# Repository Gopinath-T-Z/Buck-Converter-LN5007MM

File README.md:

# DC Buck-Converter (12V–75V → 10V, 400mA)

A KiCad-designed DC buck-boost converter using the LN5007MM PWM 
controller IC.

## Specifications
- Input Voltage  : 12V to 75V
- Output Voltage : 10V (regulated)
- Output Current : 400mA
- Controller IC  : LN5007MM
- Schottky Diode : SS110 (1A / 100V)
- Inductor       : L1 - 100µF
- PCB Tool       : KiCad EDA 9.0.7

## Block Description
| Block | Function |
|-------|----------|
| Input Power Stage | Input filtering, decoupling caps (C1, C5), R2 divider |
| PWM Controller Stage | LN5007MM, feedback resistor R5 |
| Output Filter Stage | L1, D1, C3/C4, R1/R4 feedback divider |

## Schematic Preview

## Status
- [x] Schematic complete
- [ ] PCB Layout
- [ ] Gerber files
- [ ] BOM (Bill of Materials)

## Tools Used
- KiCad EDA

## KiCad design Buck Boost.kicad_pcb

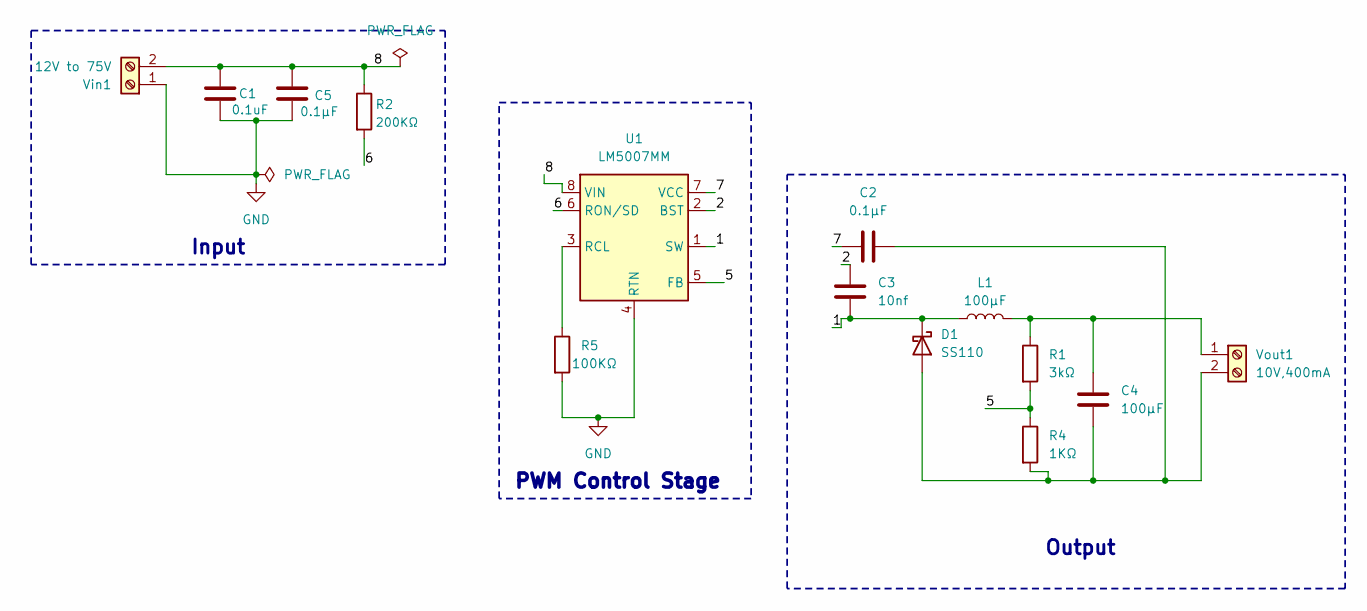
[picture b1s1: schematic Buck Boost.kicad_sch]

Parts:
C1: 0.1uF; C_0805_2012Metric
C2, C5: 0.1µF; C_0805_2012Metric
C3: 10nf; C_0805_2012Metric
C4: 100µF; C_Elec_6.3x5.4
D1: SS110; D_SMA
L1: 100µF; L_10.4x10.4_H4.8
R1: 3kΩ; R_0805_2012Metric
R2: 200KΩ; R_0805_2012Metric
R4: 1KΩ; R_0805_2012Metric
R5: 100KΩ; R_0805_2012Metric
U1: LM5007MM; MSOP-8_3x3mm_P0.65mm
Vin1: 12V to 75V; TerminalBlock_Phoenix_MKDS-1,5-2-5.08_1x02_P5.08mm_Horizont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
Vout1: 10V,400mA; TerminalBlock_Phoenix_MKDS-1,5-2-5.08_1x02_P5.08mm_Horizont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

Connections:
/1: C3.2, D1.1 (K), L1.1, U1.1 (SW)
/2: C3.1, U1.2 (BST)
/5: R1.2, R4.1, U1.5 (FB)
/6: R2.2, U1.6 (RON/SD)
/7: C2.1, U1.7 (VCC)
/8: C1.1, C5.1, R2.1, U1.8 (VIN), Vin1.2
GND: C1.2, C5.2, R5.2, U1.4 (RTN), Vin1.1
unnamed: C2.2, C4.2, D1.2 (A), R4.2, Vout1.2
unnamed: R5.1, U1.3 (RCL)
unnamed: C4.1, L1.2, R1.1, Vout1.1

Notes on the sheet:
PWM Control Stage
Output
Input

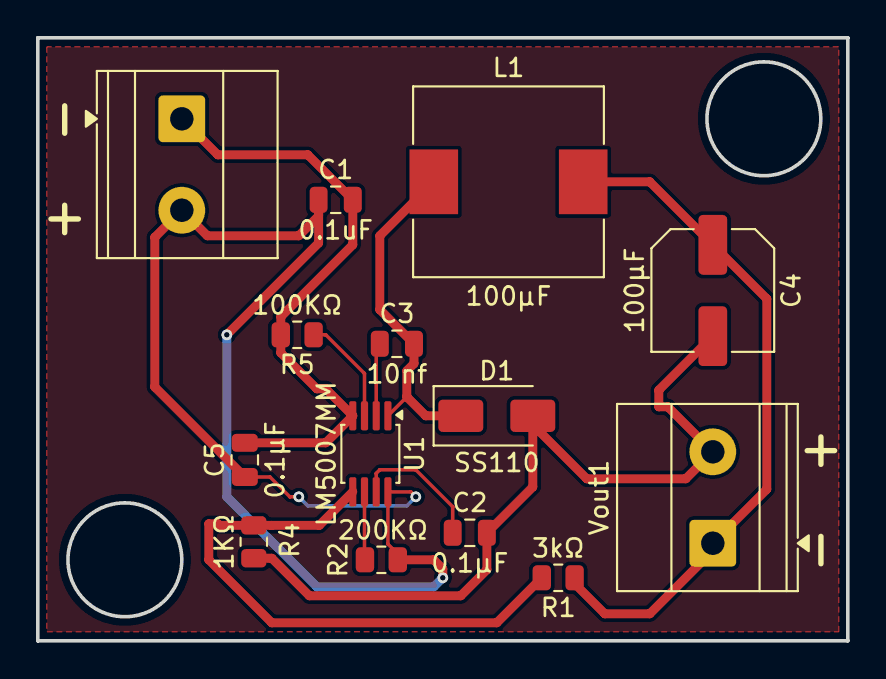
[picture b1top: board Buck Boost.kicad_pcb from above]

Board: 2 copper layers, 45.0 x 33.5 mm, 14 parts (0 on the bottom side), 10 nets.
